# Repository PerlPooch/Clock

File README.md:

# Hardware

You can power Clock via the NodeMCU micro-USB port, but it is preferable to provide +5V power via the on-board connector or terminal J1. Driving the LEDs brighter than 50% when powered via the micro-USB connector may damage the NodeMCU.

A ring of 60 WS2812B LEDs are connected to J5 or J2 (but not both). Pin 1 is ground, Pin 2 is data, Pin 3 is +5. See [[RGB Clock Controller/Schematic.pdf][The Schematic]] for details. 

Dual connectors J3 are provided for an optional small OLED display. Select the header that matches the orientation of the display.

# Software 2.11

## Wifi Configuration

If there is no configuration present or Clock is powered-on with button (SW3) depressed, Clock enters WiFi configuration mode.

In this mode, Clock will create a WiFi access point with the SSID `Clock xx:xx:xx:xx:xx:xx`. Join this AP with the password `12345678` and you will be presented with menus through which you can select and join an Internet-connected AP.

Once configured, Clock will reboot.

## USB-Serial Access

Clock will provide a serial interface via USB at 115200/8/n/1.

## OpenWeather

If you have an OpenWeather key, Clock will obtain the weather by making requests to 

    GET http://api.openweathermap.org/data/2.5/weather

using the configured key. You must set `owAppKey`, `latitude`, and `longitude`.

## Start Up

Clock will test the display, connect to the configured WiFi AP, and retrieve the current date and time via NTP. 

## Configuration

You can reach Clock via HTTP at its address. If you don't know the address that was assigned, you can enter WiFi Configuration mode and view the assigned IP address. Alternatively, the assigned IP address is available via the Serial connection upon start up.

### Query Values and Status

Making a GET request to / will return a JSON payload of the current configuration. 

    http://<clockip>/

| Field                | Meaning / Range                                                              |
| :------------------- | :--------------------------------------------------------------------------- |
| **"sleepRemaining"** | `<int>` – Remaining **sleep time** in seconds                                |
| **"timezone"**       | `<int>` – **Timezone offset** from OpenWeather data                          |
| **"nextNTPUpdate"**  | `<int>` – Seconds until the next **NTP time update**                         |
| **"nextOWUpdate"**   | `<int>` – Seconds until the next **OpenWeather update**                      |
| **"temperature"**    | `<int>` – Current **temperature (°F)**                                       |
| **"lastOWResponse"** | `<int>` – Last **HTTP response code** from OpenWeather                       |
| **"time"**           | `<string>` – Current **time**                                                |
| **"display"**        | `<string>` – Display state (**Day**, **Night**, **Sleep**, or **Preparing**) |
| **"version"**        | `<string>` – Clock **firmware version**                                      |

### Set Values

Making a GET request with a query-string can configure the options. 

For example, to set the dim intensity and bright intensity for both daytime and nighttime modes:

    http://clockip/?dim=7&bright=20&dimNight=7&brightNight=20

| Option             | Meaning / Range                                                  |
| :----------------- | :--------------------------------------------------------------- |
| **"dim"**          | `0 .. 100` – Brightness of standard dots during **Day time**     |
| **"bright"**       | `0 .. 100` – Brightness of tick dots during **Day time**         |
| **"dimNight"**     | `0 .. 100` – Brightness of standard dots during **Night time**   |
| **"brightNight"**  | `0 .. 100` – Brightness of tick dots during **Night time**       |
| **"temp"**         | `0 .. 100` – Brightness of temperature dot when **sleeping**     |
| **"hue"**          | `0 .. 100` – Universal **color shift** to apply                  |
| **"coldHue"**      | `0 .. 100` – Color of temperature dot when **temperature < 60°** |
| **"warmHue"**      | `0 .. 100` – Color of temperature dot when **temperature > 60°** |
| **"nightHour"**    | `0 .. 23` – Hour to **start Night time**                         |
| **"dayHour"**      | `0 .. 23` – Hour to **end Night time**                           |
| **"owAppKey"**     | `<string>` – **OpenWeather API Key**                             |
| **"latitude"**     | `<float>` – Location **Latitude**                                |
| **"longitude"**    | `<float>` – Location **Longitude**                               |
| **"displaySleep"** | `<int>` – Sleep the display for this many **seconds**            |
| **"reboot"**       | `<>` – **Reboot**                              |

## OTA Firmware Update

    GET http://<clockip>/_ac/update

## WiFi Configuration Changes

    GET http://<clockip>/_ac/

# Building

Clock is based on the (now old) NodeMCU 12E ESP8266 board. 

## Libraries

The Arduino community is great, offering many useful libraries to build upon. This project requires:

* SPI
* Wire
* Adafruit GFX Library
* Adafruit SSD1306
* arduino-timer
* ArduinoJson
* ESP8266WiFi
* ESP8266WebServer
* AutoConnect
* LittleFS
* ESP8266HTTPClient
* NeoPixelBus by Makuna
* NTPClient

These Libraries, in turn, require:

* Adafruit BusIO
* DNSServer
* EEPROM
* PageBuilder
* SD
* SDFS
* ESP8266SdFat
* Ticker
* ESP8266httpUpdate

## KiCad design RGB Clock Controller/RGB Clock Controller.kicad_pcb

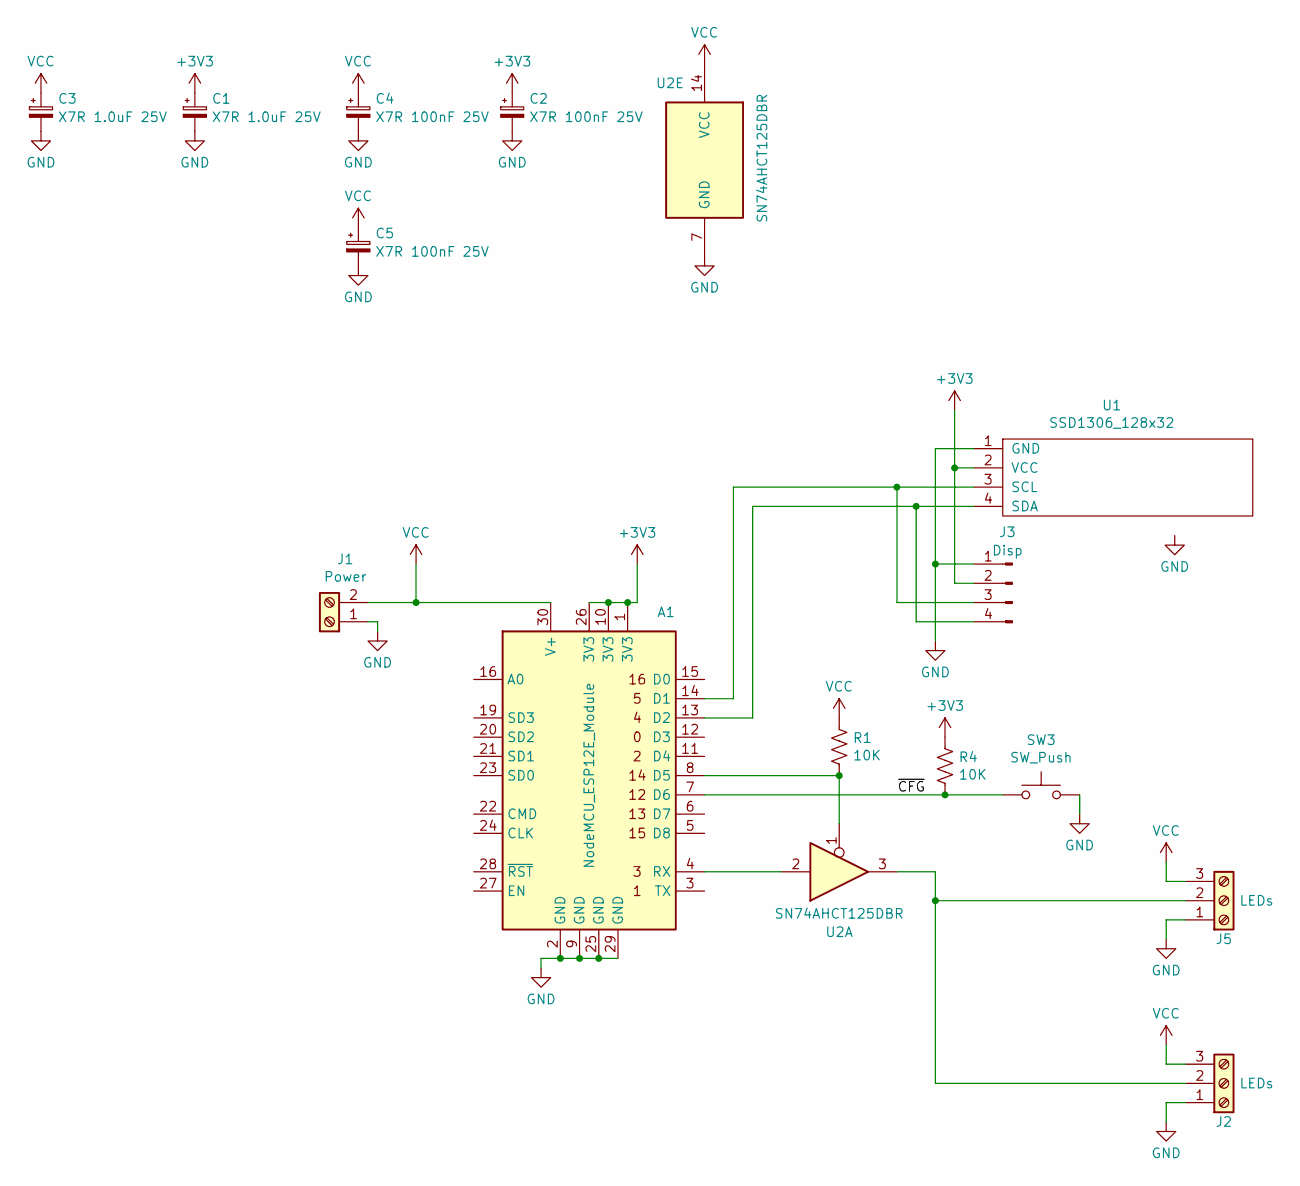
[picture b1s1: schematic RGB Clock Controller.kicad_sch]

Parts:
A1: NodeMCU_ESP12E_Module; NodeMCU
C1, C3: X7R 1.0uF 25V; C_1206_3216Metric_Pad1.33x1.80mm_HandSolder
C2, C4, C5: X7R 100nF 25V; C_0805_2012Metric_Pad1.18x1.45mm_HandSolder
J1: Power; TerminalBlock_Phoenix_MPT-0,5-2-2.54_1x02_P2.54mm_Horizontal
J2, J5: LEDs; TerminalBlock_Phoenix_MPT-0,5-3-2.54_1x03_P2.54mm_Horizontal
J3: Disp; PinHeader_1x04_P2.54mm_Vertical
R1, R4: 10K; R_1206_3216Metric_Pad1.30x1.75mm_HandSolder
SW3: SW_Push; SW_PUSH_6mm_H4.3mm
U1: SSD1306_128x32; PinHeader_1x04_P2.54mm_Vertical
U2: SN74AHCT125DBR; SSOP-14_5.3x6.2mm_P0.65mm

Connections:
+3V3: A1.1 (3V3), A1.10 (3V3), A1.26 (3V3), C1.1, C2.1, J3.2, R4.1, U1.2 (VCC)
/~CFG: A1.7 (D6), R4.2, SW3.1
GND: A1.2 (GND), A1.9 (GND), A1.25 (GND), A1.29 (GND), C1.2, C2.2, C3.2, C4.2, C5.2, J1.1, J2.1, J3.1, J5.1, SW3.2, U1.1 (GND), U2.7 (GND)
unnamed: A1.14 (D1), J3.3, U1.3 (SCL)
unnamed: A1.13 (D2), J3.4, U1.4 (SDA)
unnamed: A1.8 (D5), R1.2, U2.1
unnamed: A1.4 (RX), U2.2
unnamed: J2.2, J5.2, U2.3
VCC: A1.30 (V+), C3.1, C4.1, C5.1, J1.2, J2.3, J5.3, R1.1, U2.14 (VCC)

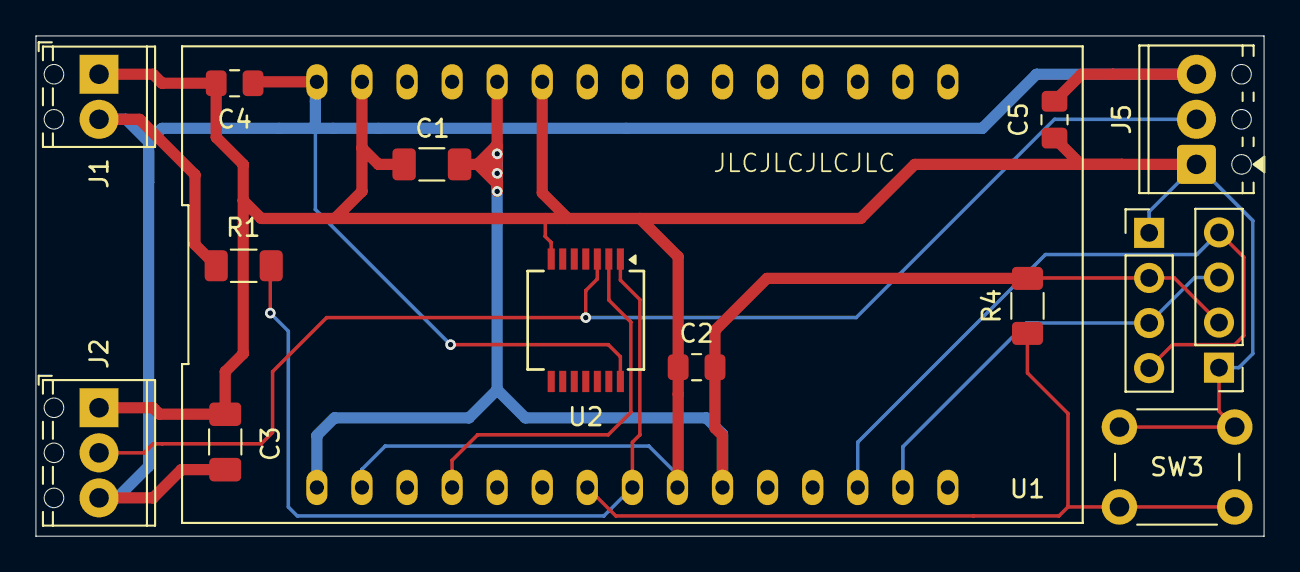
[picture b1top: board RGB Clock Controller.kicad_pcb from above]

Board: 2 copper layers, 69.2 x 28.2 mm, 15 parts (0 on the bottom side), 9 nets.

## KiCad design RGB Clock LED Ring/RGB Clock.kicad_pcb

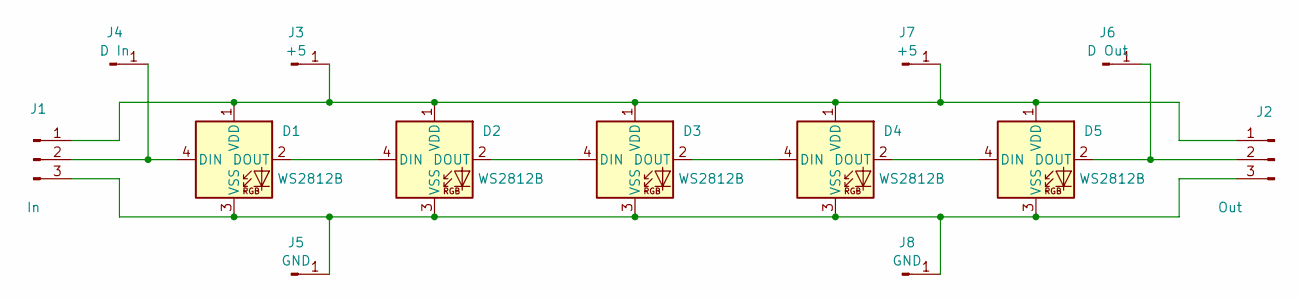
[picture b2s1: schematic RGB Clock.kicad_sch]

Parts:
D1, D2, D3, D4, D5: WS2812B; LED_WS2812B_PLCC4_5.0x5.0mm_P3.2mm
J1: In; Connector 2.0mm 5.0mm on 2.5mm
J2: Out; Connector 2.0mm 5.0mm on 2.5mm
J3, J7: +5; Pin_D1.0mm_L10.0mm
J4: D In; Pin_D1.0mm_L10.0mm
J5, J8: GND; Pin_D1.0mm_L10.0mm
J6: D Out; Pin_D1.0mm_L10.0mm

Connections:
unnamed: D1.4 (DIN), J1.2, J4.1
unnamed: D1.2 (DOUT), D2.4 (DIN)
unnamed: D1.1 (VDD), D2.1 (VDD), D3.1 (VDD), D4.1 (VDD), D5.1 (VDD), J1.1, J2.1, J3.1, J7.1
unnamed: D1.3 (VSS), D2.3 (VSS), D3.3 (VSS), D4.3 (VSS), D5.3 (VSS), J1.3, J2.3, J5.1, J8.1
unnamed: D2.2 (DOUT), D3.4 (DIN)
unnamed: D3.2 (DOUT), D4.4 (DIN)
unnamed: D4.2 (DOUT), D5.4 (DIN)
unnamed: D5.2 (DOUT), J2.2, J6.1

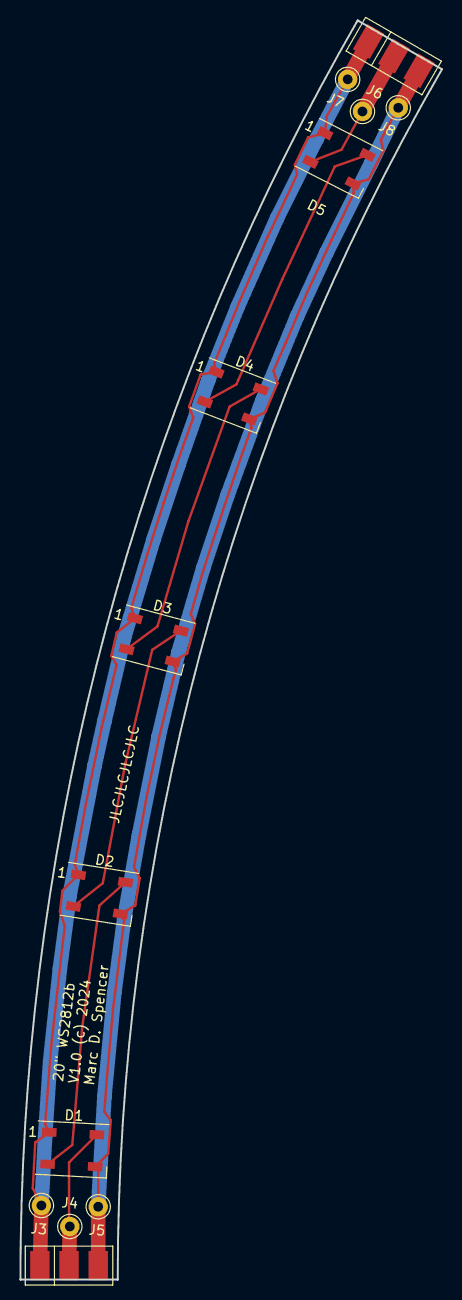
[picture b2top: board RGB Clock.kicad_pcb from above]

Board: 2 copper layers, 43.4 x 129.5 mm, 13 parts (0 on the bottom side), 8 nets.

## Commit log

2025-11-05 Renaming Clock.md to README.md
2025-11-05 Added LED Ring KiCAD Document
2025-11-05 Added Clock Controller KiCAD Document
2025-11-05 Added Fabrication files
2025-11-05 Corrected polarity mistake on level-shifter. Adjusted layout slightly
2025-11-06 Moved PDFs to top level
2025-11-06 Update README.md
    Speling Fixes :-)
2025-11-16 Added library dependencies to README

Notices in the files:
RGB Clock Controller/RGB Clock Controller.kicad_pcb:
(c) 2005 Marc D. Spencer
RGB Clock LED Ring/RGB Clock.kicad_pcb:
V1.0 (c) 2024
